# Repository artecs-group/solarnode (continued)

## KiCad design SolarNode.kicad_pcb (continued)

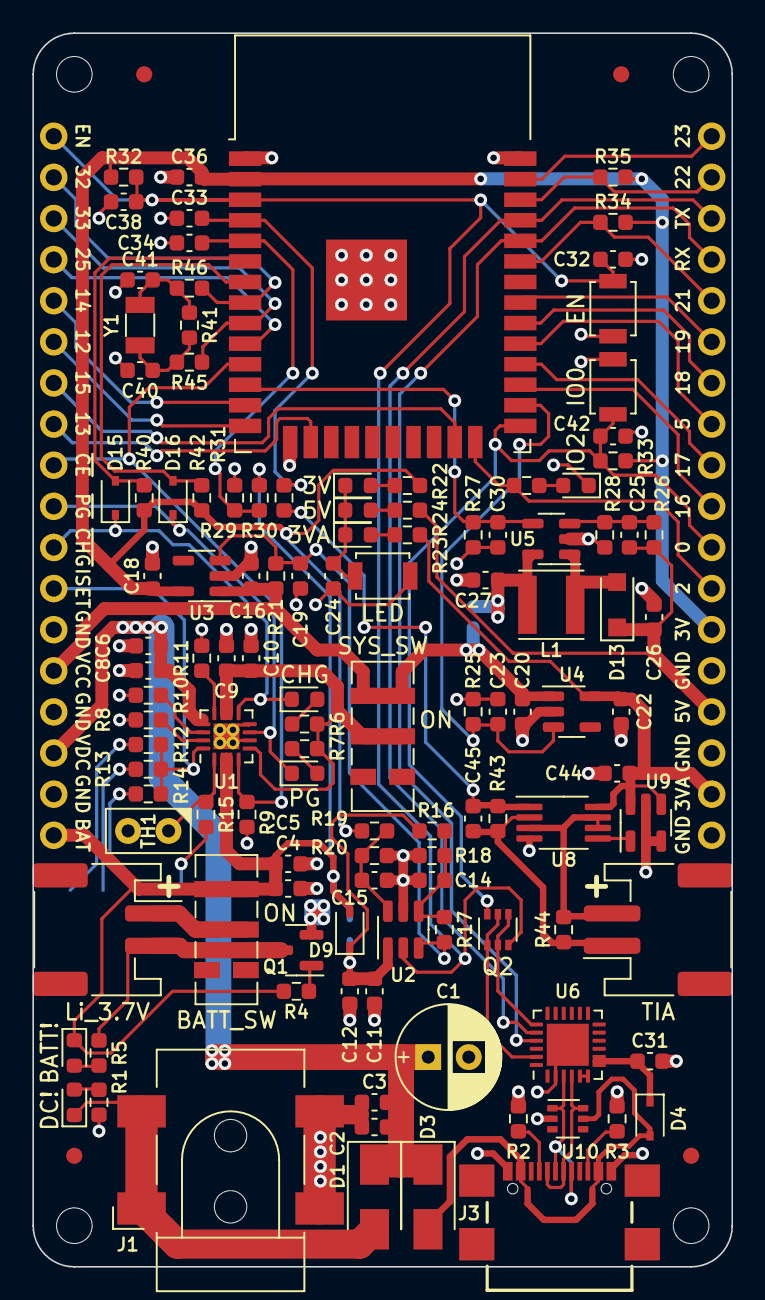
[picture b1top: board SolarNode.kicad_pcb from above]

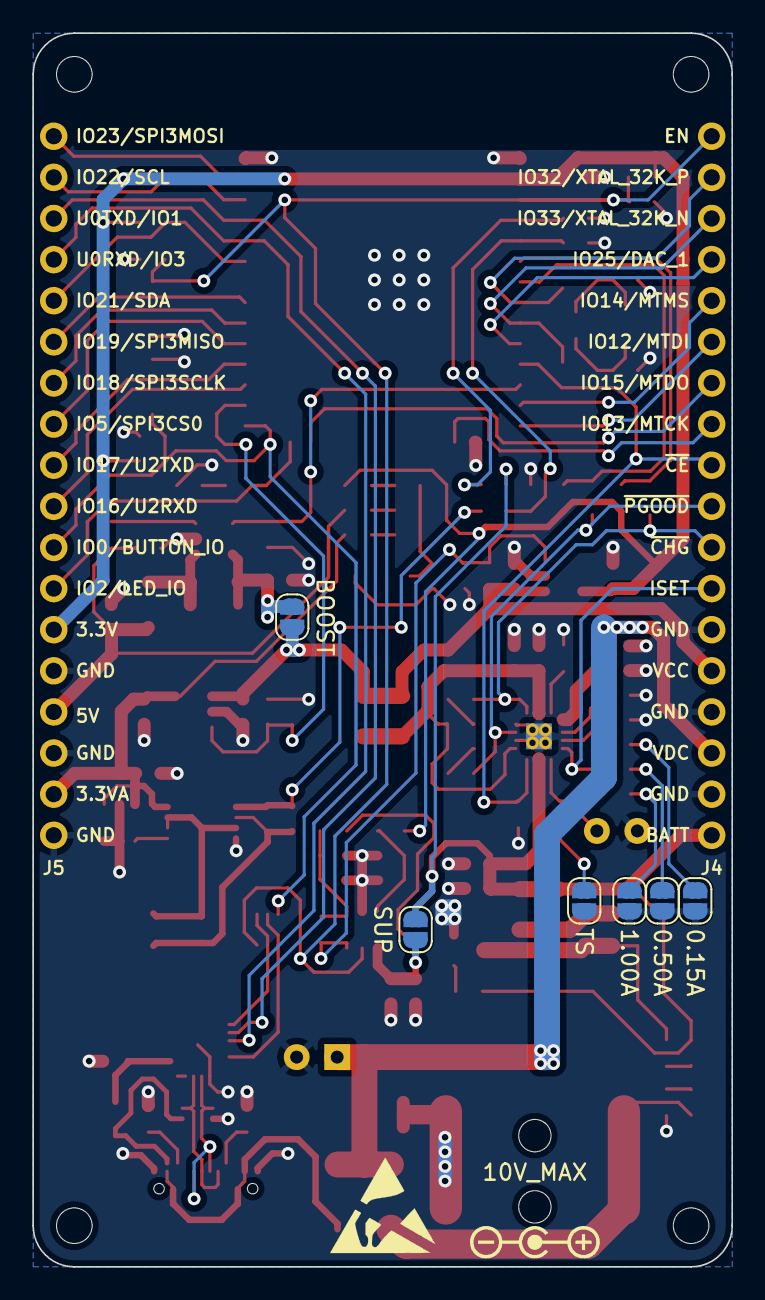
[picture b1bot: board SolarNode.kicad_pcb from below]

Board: 2 copper layers, 43.2 x 76.2 mm, 133 parts (8 on the bottom side), 81 nets.
